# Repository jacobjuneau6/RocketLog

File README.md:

# RocketLog
RocketLog is a rocket altimeter designed to fit in the estes So Long rocket and provide attitude and altitude data on the rocket logging to redundant internal flash.
# Pictures

# Design
Click the image to open the interactive KiCanvas viewer.
# Why
I have flown by custom painted and modified So Long rocket many times but have only been able to estimate the appogee and forces experienced. As I want to aluch sime more delicate payloads in the future, I want to see the forces that would be experienced by the payload before I fly some more delicate payloads.
# BOM
| Reference | Value | DigiKey_Part_Number | Link | Cost |
| --- | --- | --- | --- | --- |
| J3 | 10118193-0001LF | 609-4616-1-ND | [Link](https://www.digikey.com/en/products/detail/amphenol-cs-fci/10118193-0001LF/2785388) | $0.58 |
| R5,R6 | RC2512JK-0710KL | YAG3394CT-ND | [Link](https://www.digikey.com/en/products/detail/yageo/RC2512JK-0710KL/5922475) | $0.60 |
| U1 | ESP32-S3-WROOM-1-N8R8 | 5407-ESP32-S3-WROOM-1-N8R8CT-ND | [Link](https://www.digikey.com/en/products/detail/espressif-systems/ESP32-S3-WROOM-1-N8R8/15295891) | $6.73 |
| U2 | TLV75533PDYDR | 296-TLV75533PDYDRCT-ND | [Link](https://www.digikey.com/en/products/detail/texas-instruments/TLV75533PDYDR/22531567) | $0.30 |
| U3 | BMP384 | 828-BMP384CT-ND | [Link](https://www.digikey.com/en/products/detail/bosch-sensortec/BMP384/13681277) | $3.75 |
| U5 | MPU-6500 | 1428-1011-1-ND | [Link](https://www.digikey.com/en/products/detail/tdk-invensense/MPU-6500/4385412) | $8.00 |
| U6 | W25Q128JVSIQ | W25Q128JVSIQ-ND | [Flash](https://www.aliexpress.us/item/3256811354152848.html?utparam-url=scene%3Asearch%7Cquery_from%3A%7Cx_object_id%3A1005011540467600%7C_p_origin_prod%3A) | $7.00 |
| PCB | Custom Boards & Stencils from JLCPCB | | | $27.00 |
| Battery | 300mAh battery | | [Battery](https://www.amazon.com/battery-Rechargeable-Lithium-Polymer-Connector/dp/B07BTTVX4Q?th=1) | $4.00 |
| Digikey Shipping | | | | $8.50 |

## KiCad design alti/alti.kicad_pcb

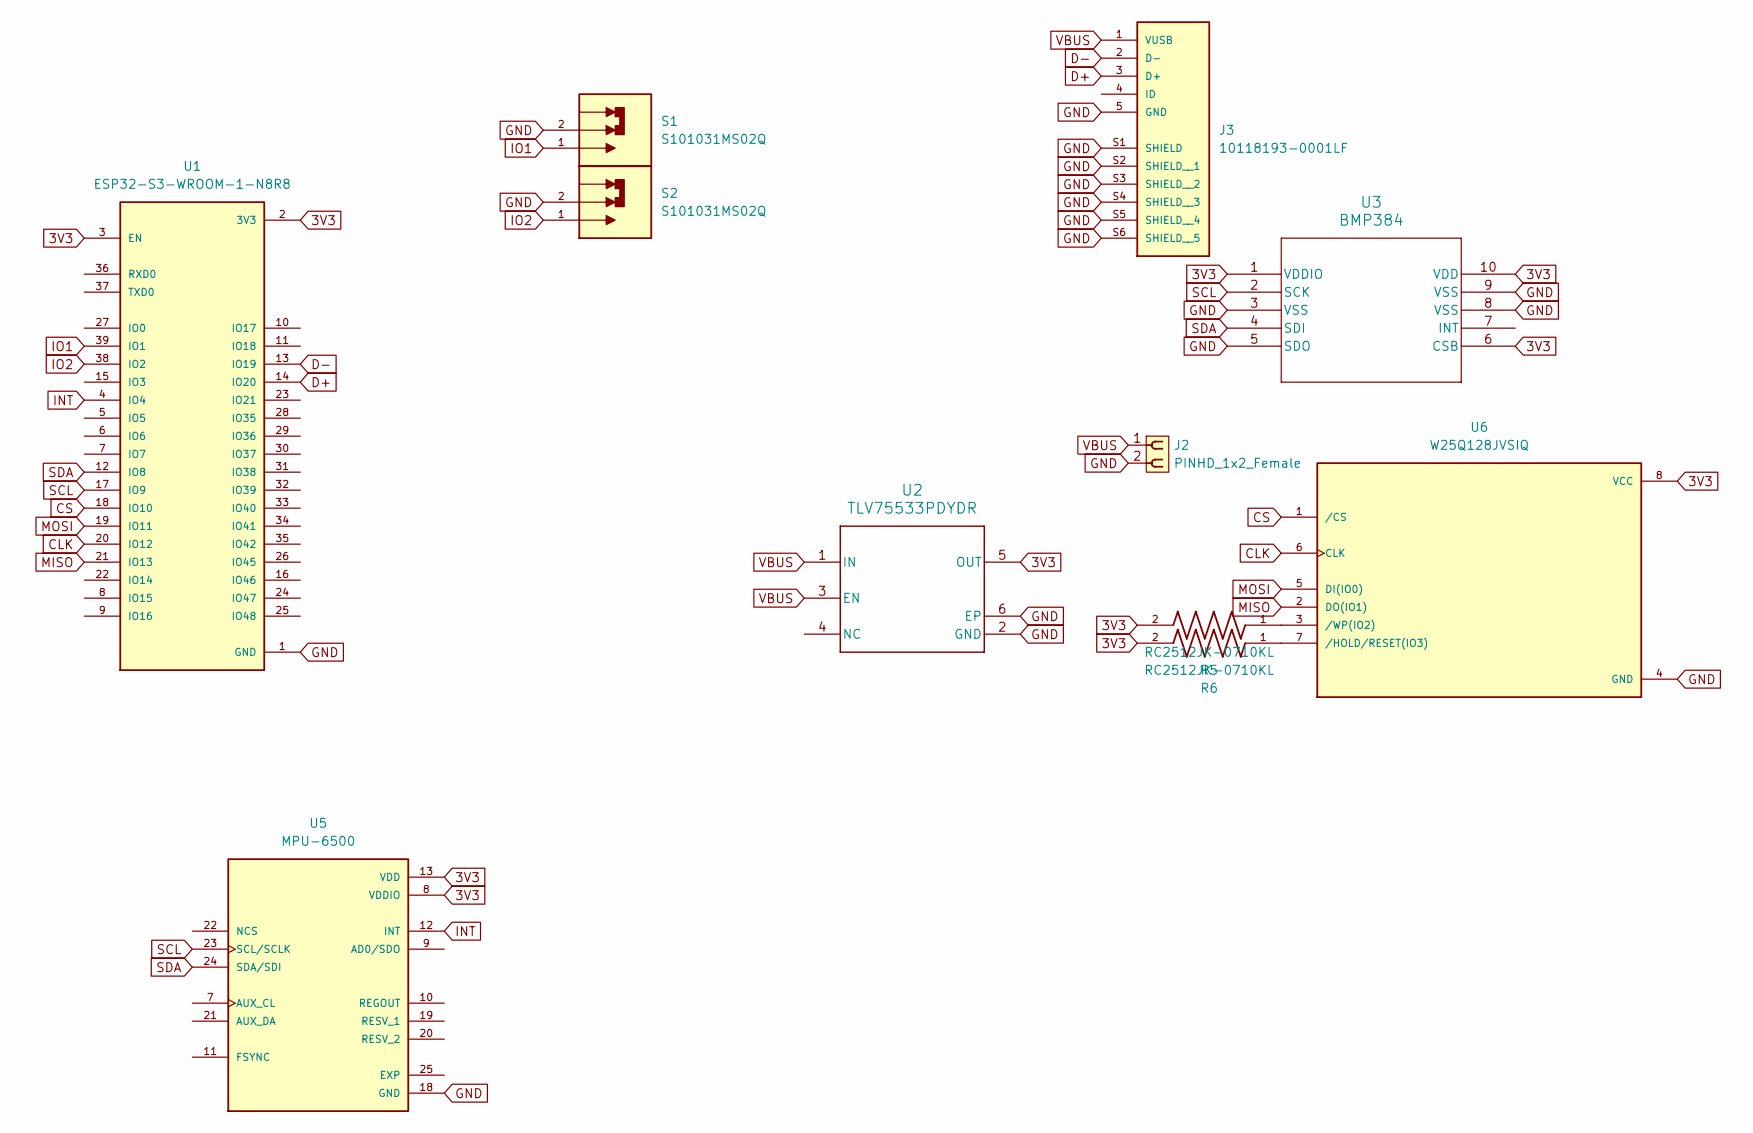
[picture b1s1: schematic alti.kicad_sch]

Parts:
J2: PINHD_1x2_Female; PinSocket_1x02_P2.54mm_Vertical
J3: 10118193-0001LF; AMPHENOL_10118193-0001LF; PARTREV E; DigiKey_Part_Number 609-4616-1-ND
R5, R6: RC2512JK-0710KL; RESC6331X65N; DigiKey_Part_Number YAG3394CT-ND
S1, S2: S101031MS02Q; PinHeader_1x02_P2.54mm_Vertical; PARTREV I; DigiKey_Part_Number CKN10658-ND
U1: ESP32-S3-WROOM-1-N8R8; XCVR_ESP32S3WROOM1N8R8; DigiKey_Part_Number 5407-ESP32-S3-WROOM-1-N8R8CT-ND
U2: TLV75533PDYDR; DYD0005A-MFG; DigiKey_Part_Number 296-TLV75533PDYDRCT-ND
U3: BMP384; LGA10_2.0X2.0X0.95_BOS; DigiKey_Part_Number 296-TLV75533PDYDRCT-ND
U5: MPU-6500; QFN40P300X300X95-25N; PARTREV 1.3; DigiKey_Part_Number 1428-1011-1-ND
U6: W25Q128JVSIQ; SOIC127P790X216-8N; PARTREV I; DigiKey_Part_Number W25Q128JVSIQ-ND

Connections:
3V3: R5.2, R6.2, U1.2 (3V3), U1.3 (EN), U2.5 (OUT), U3.1 (VDDIO), U3.6 (CSB), U3.10 (VDD), U5.8 (VDDIO), U5.13 (VDD), U6.8 (VCC)
CLK: U1.20 (IO12), U6.6 (CLK)
CS: U1.18 (IO10), U6.1 (/CS)
D+: J3.3 (D+), U1.14 (IO20)
D-: J3.2 (D-), U1.13 (IO19)
GND: J2.2, J3.5 (GND), J3.S1 (SHIELD), J3.S2 (SHIELD__1), J3.S3 (SHIELD__2), J3.S4 (SHIELD__3), J3.S5 (SHIELD__4), J3.S6 (SHIELD__5), S1.2, S2.2, U1.1 (GND), U1.40 (GND), U1.41_1 (GND), U1.41_2 (GND), U1.41_3 (GND), U1.41_4 (GND), U1.41_5 (GND), U1.41_6 (GND), U1.41_7 (GND), U1.41_8 (GND), U1.41_9 (GND), U2.2 (GND), U2.6 (EP), U3.3 (VSS), U3.5 (SDO), U3.8 (VSS), U3.9 (VSS), U5.18 (GND), U6.4 (GND)
INT: U1.4 (IO4), U5.12 (INT)
IO1: S1.1, U1.39 (IO1)
IO2: S2.1, U1.38 (IO2)
MISO: U1.21 (IO13), U6.2 (DO(IO1))
MOSI: U1.19 (IO11), U6.5 (DI(IO0))
unnamed: R6.1, U6.7 (/HOLD/RESET(IO3))
unnamed: R5.1, U6.3 (/WP(IO2))
SCL: U1.17 (IO9), U3.2 (SCK), U5.23 (SCL/SCLK)
SDA: U1.12 (IO8), U3.4 (SDI), U5.24 (SDA/SDI)
VBUS: J2.1, J3.1 (VUSB), U2.1 (IN), U2.3 (EN)

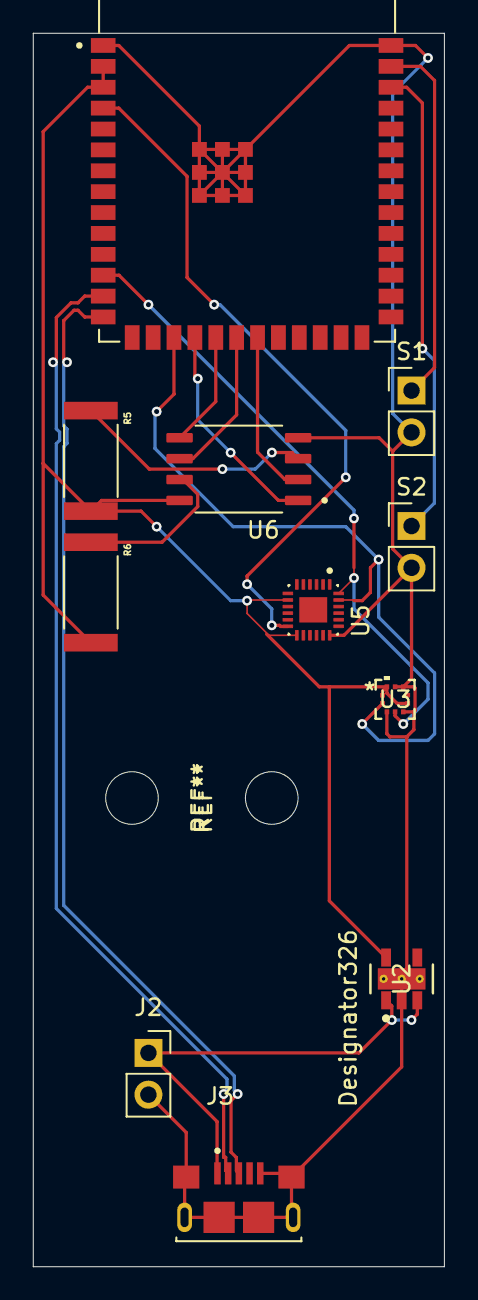
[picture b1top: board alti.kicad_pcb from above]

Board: 2 copper layers, 25.0 x 75.0 mm, 11 parts (0 on the bottom side), 16 nets.

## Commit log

2026-06-19 add PCB
2026-06-20 add flight code
2026-06-20 README
2026-06-20 Update readme with BOM info
2026-06-21 Add pictures
2026-06-26 update PCB based on feedback
